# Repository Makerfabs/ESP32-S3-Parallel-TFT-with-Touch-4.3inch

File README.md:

# Makerfabs ESP32-S3 Parallel TFT with Touch 4.3inch

```c++
/*
Version:        V1.1
Author:            Vincent
Create Date:    2022/12/29
Note:
    2023/4/15 V1.2: Update V2.0 hardware.
    2023/1/10 V1.1: Update code to match the V1.3 hardware.
*/
```

[TOC]

# Makerfabs

[Makerfabs home page](https://www.makerfabs.com/)

[Makerfabs Wiki](https://wiki.makerfabs.com/)

# Makerfabs ESP32-S3 Parallel TFT with Touch 4.3inch

## Intruduce

Product Link ：[ESP32-S3 Parallel TFT with Touch 4.3"](https://www.makerfabs.com/esp32-s3-parallel-tft-with-touch-4-3-inch.html)

Wiki Link : [ESP32-S3 Parallel 4.3 TFT with Touch](http://wiki.makerfabs.com/ESP32_S3_Parallel_4.3_TFT_with_Touch.html)

This ESP32 4.3 inch IPS display could be an ideal displayer& controller for IoT applications. Its high lightness IPS display with a resolution of 800*480 makes the display effect beautiful, together with 5 points capacitive touch, great for applications such as home automation; There onboard SD card and RTC, to make it possible to record/play filed data. Also, there 2 Mabee/ Grove connectors, so the users can connect kinds of sensors to this board, to create personal prototype projects instantly.

The ESP32-S3 has WiFi& Bluetooth 5.0, and 8M PSRAM ESP32-S3 is used in this product, with 16M flash, to make it competent for more advanced applications.

## Feature

- Controller: ESP32-S3-WROOM-1, PCB Antenna, 16MB Flash, 8MB PSRAM, ESP32-S3-WROOM-1-N16R8
- On Board RTC
- Wireless: Wifi& Bluetooth 5.0
- LCD: 4.3 inch High Lightness IPS
- FPS: >30
- Resolution: 800*480
- LCD interface: RGB 565
- Touch Panel: 5 Points Touch, Capacitive
- Touch Panel Driver: GT911
- USB: Dual USB Type-C(one for USB-to-UART and one for native USB)
- USB to UART Chip: CP2104
- Power Supply: USB Type-C 5.0V(4.0V~5.25V)
- Button: Flash button and reset button
- Mabee interface: 1*I2C;1*GPIO
- MicroSD: Yes
- Arduino support: Yes
- Type-C Power Delivery: Not Supported
- Operation temperature: -40℃ to +85℃

## Version Attention

### V2.0

The codes has not been modified yet, please wait a little.

Still working...

|           | V2.0 | V1.3 |
| --------- | ---- | ---- |
| LCD_BLK   | NULL | 2    |
| I2S_DIN   | 19   | NULL |
| I2S_BCLK  | 20   | NULL |
| I2S_LRCLK | 2    | NULL |
|           |      |      |

Now the screen has no backlight PWM adjustment function, the pins are assigned to I2S. By default, the hardware backlight is always on.

### V1.3

V1.3 switches the touch screen RST and INT pins compared to V1.1 hardware.

```c++
// Hardware V1.3
#define TOUCH_GT911_SCL 18
#define TOUCH_GT911_SDA 17
#define TOUCH_GT911_INT -1
#define TOUCH_GT911_RST 38
```

### V1.1

If the silk screen on the back of your hardware is V1.1, follow the Branch V1.1 procedure.

# Code

## Complier Option

- Install board : ESP32 (Version 2.0.4)
- Install libraries：

- Use type-c use cable connect USB-TTL to PC.
- Select "ESP32-S3 DEV Module"
- Select PSRAM "OPI PSRAM"

"mf_Lvgl" library is modified from Lvgl library (version 8.3.2). 

Please unzip "lib/mf_Lvgl.zip" and copy to arduino library directory.

## Factory test program

examples\esp32s3_4.3_tft_fw_test

You can run this file test if you feel that your hardware is not working properly. You need to copy the images from the Images folder to the included TF card.

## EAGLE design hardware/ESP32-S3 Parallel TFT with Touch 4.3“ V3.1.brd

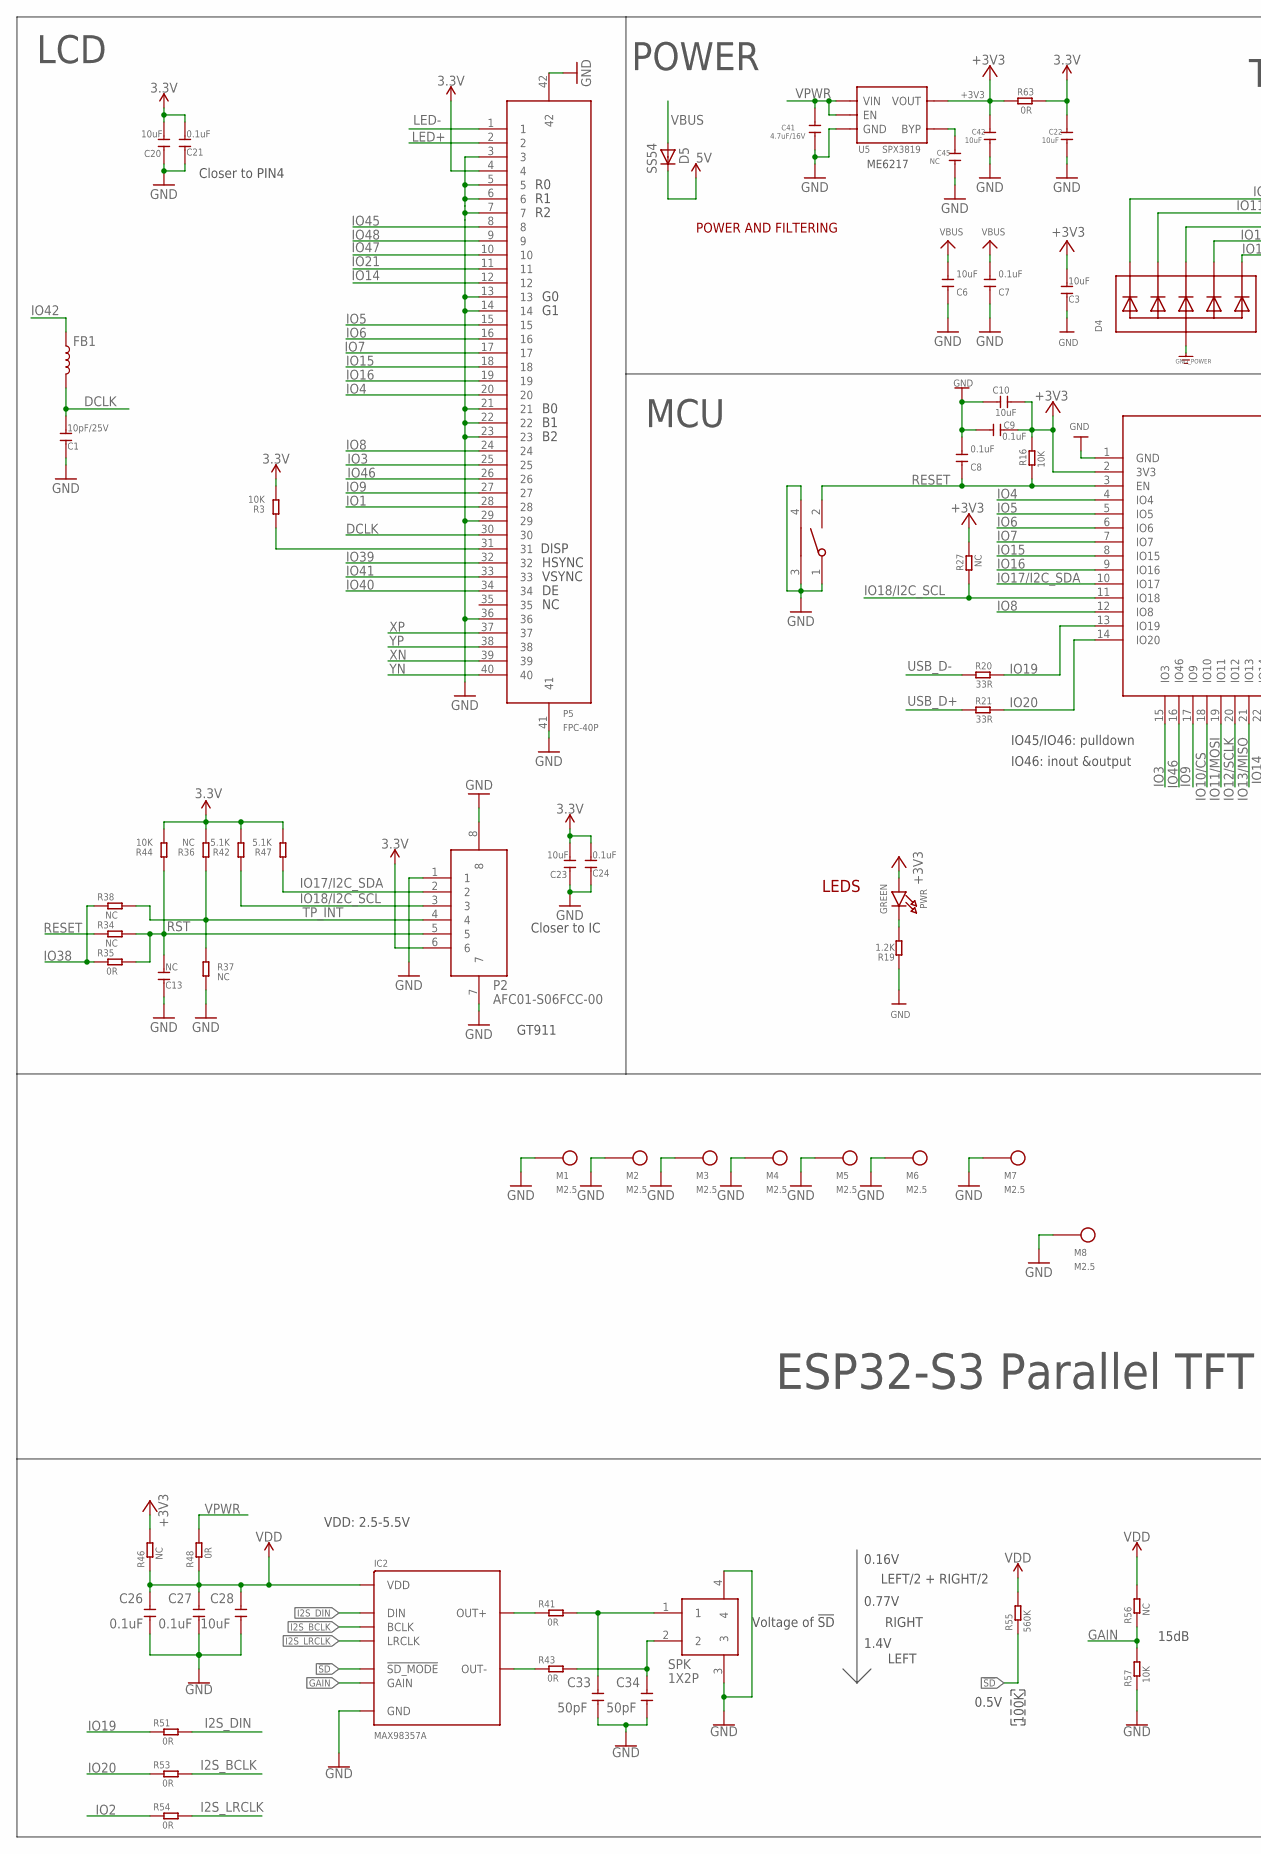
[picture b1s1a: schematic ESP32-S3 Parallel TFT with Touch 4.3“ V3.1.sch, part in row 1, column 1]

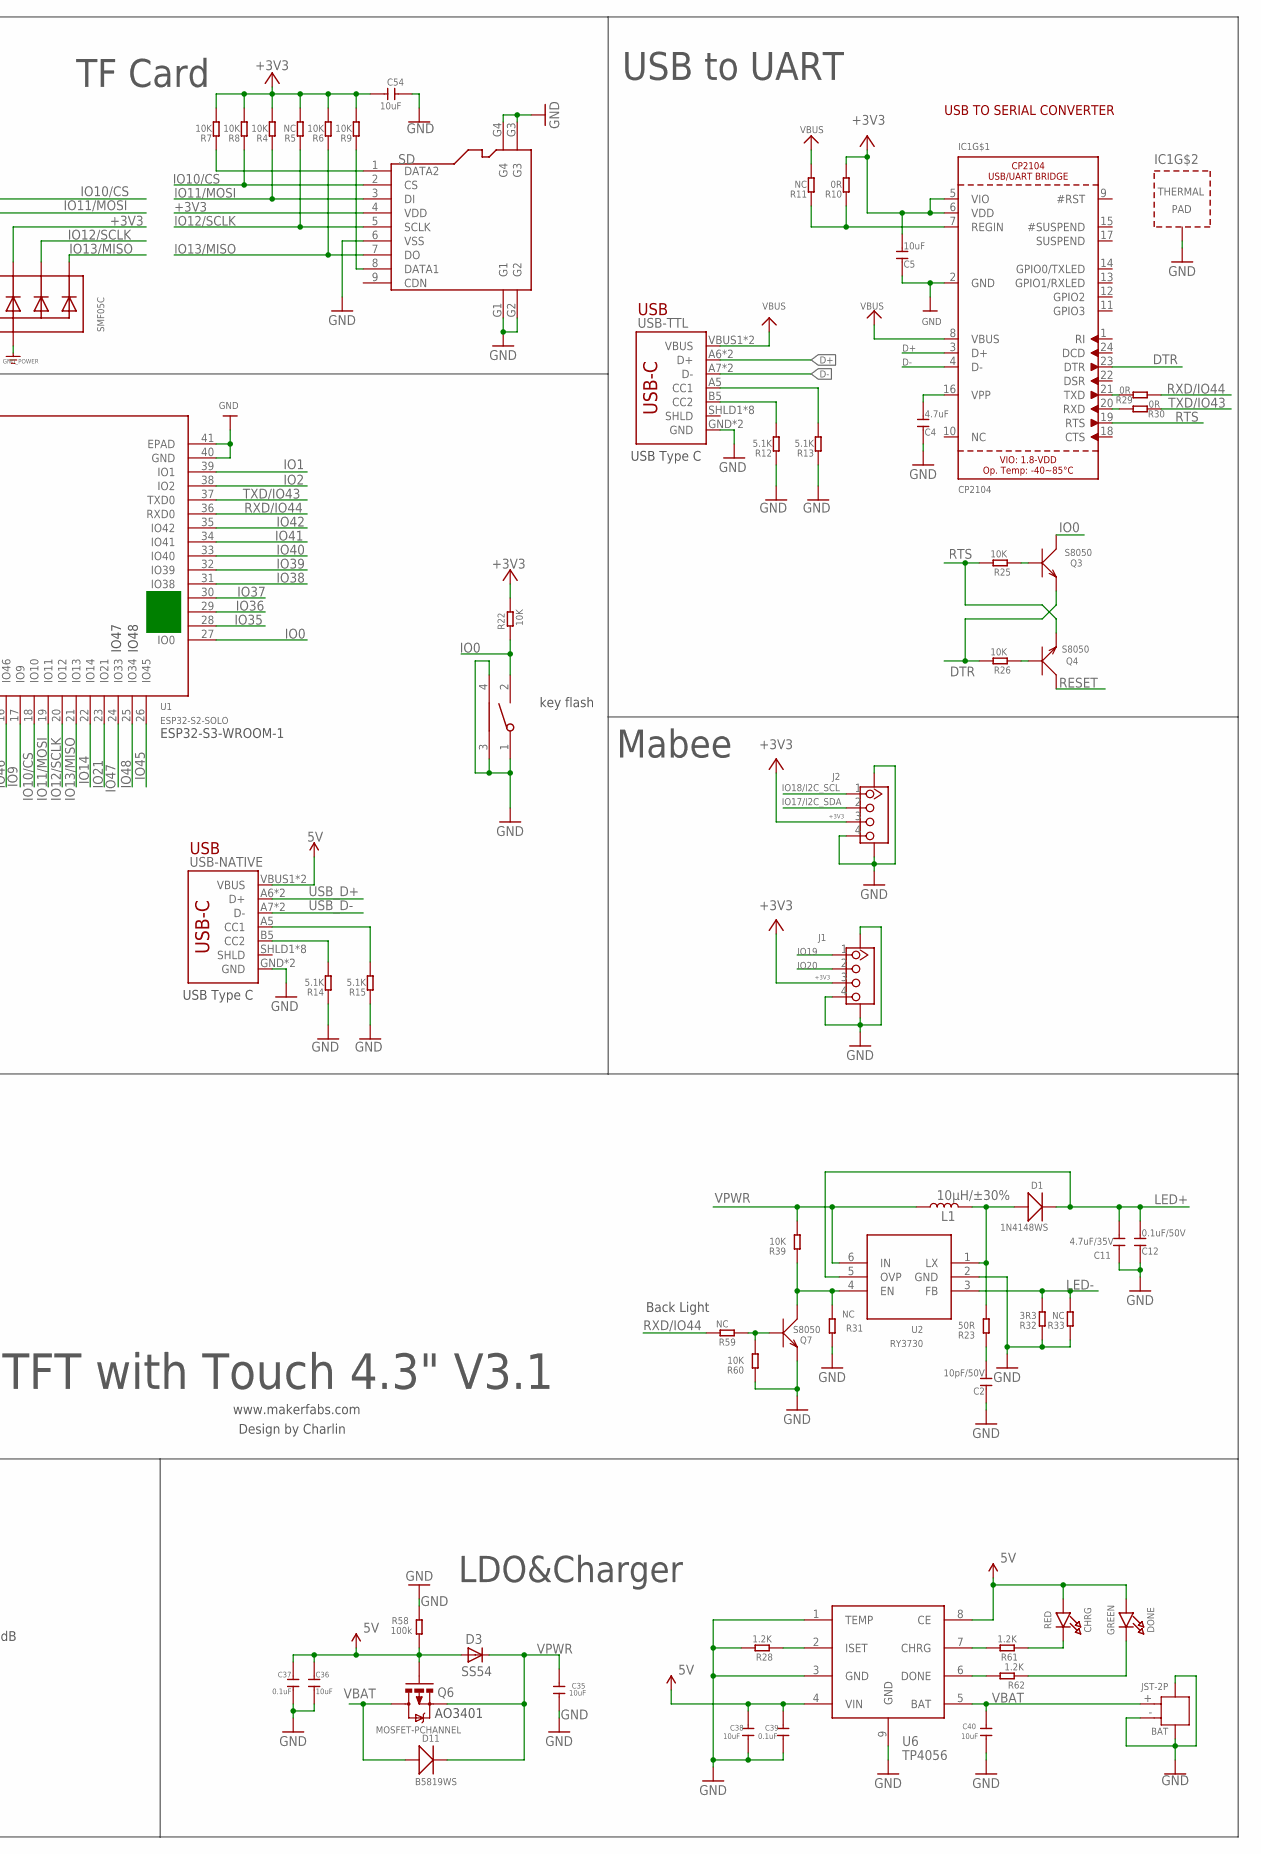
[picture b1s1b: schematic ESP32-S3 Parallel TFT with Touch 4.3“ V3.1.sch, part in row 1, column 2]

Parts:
BAT: JST-2P; HW2-SMD-2.0-90D
BOOT: TS24CA; 2*4*3.5MM
C1: 10pF/25V; DISCRETE_C0603
C2: 10pF/50V; DISCRETE_C0603
C3, C5, C6, C10, C20, C23, C54: 10uF; DISCRETE_C0603
C4: 4.7uF; DISCRETE_C0603
C7, C8, C9, C21, C24: 0.1uF; DISCRETE_C0603
C11: 4.7uF/35V; DISCRETE_C1206
C12: 0.1uF/50V; DISCRETE_C0603
C13: NC; DISCRETE_C0603
C22, C28, C35, C36, C38, C40, C42: 10uF; 0603
C26, C27, C37, C39: 0.1uF; 0603
C33, C34: 50pF; 0603
C41: 4.7uF/16V; 0603
C45: NC; 0603
CHRG: RED; CHIPLED_0805_NOOUTLINE
D1: 1N4148WS; SOD323
D3, D5: SS54; DO-214AC
D4: SMF05C; SOT363
D11: B5819WS; SOD323
DONE: GREEN; CHIPLED_0805_NOOUTLINE
FB1: INDUCTORFB-30OHM; 0603
IC1: CP2104; QFN24_4MM_SMSC
IC2: MAX98357A; TQFN-16
J1, J2: GROVE-CONNECTOR-SMD'90D'; HW4-SMD-2.0-90D
L1: 10µH/±30%; CR54
M1, M2, M3, M4, M5, M6, M7, M8: M2.5
P2: AFC01-S06FCC-00; SMD8-50P-740L535W
P5: FPC-40P; SMD42-50P-2560L490W
PWR: GREEN; CHIPLED_0805_NOOUTLINE
Q3, Q4, Q7: S8050; SOT23
Q6: MOSFET-PCHANNEL; SOT23-3
R3, R4, R6, R7, R8, R9, R39, R44, R60: 10K; DISCRETE_R0603
R5, R11, R31, R33, R36, R37, R59: NC; DISCRETE_R0603
R10: 0R; DISCRETE_R0603
R12, R13, R14, R15, R42, R47: 5.1K; DISCRETE_R0603
R16, R22, R25, R26, R57: 10K; R0603
R19: 1.2K; DISCRETE_R0603
R20, R21: 33R; R0603
R23: 50R; DISCRETE_R0603
R27, R34, R38, R46, R56: NC; R0603
R28, R61, R62: 1.2K; R0603
R29, R30, R35, R41, R43, R48, R51, R53, R54, R63: 0R; R0603
R32: 3R3; DISCRETE_R0603
R55: 560K; R0603
R58: 100k; R0603
RST: TS24CA; 2*4*3.5MM
SD: HOLDER-MICROSD-9P; 9P-SMD-W/-RING
SPK: 1X2P; 1X2P-SMT1.25MM
U1: ESP32­S2­SOLO; ESP32-­S2-­SOLO
U2: RY3730; SOT23-6
U5: SPX3819; SOT23-5
U6: TP4056; SOP8-1.27P
USB-NATIVE: USB_C5; USB-C-16P-5
USB-TTL: USB_C5; USB-C-16P-5

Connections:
3.3V: C20.2, C21.2, C22.1, C23.2, C24.2, P2.6, P5.4, R3.2, R36.2, R42.2, R44.2, R47.2, R63.2
5V: C36.2, C37.1, C38.1, C39.1, CHRG.A, D3.A, D5.C, DONE.A, Q6.1 (G), R58.1, U6.4 (VIN), U6.8 (CE), USB-NATIVE.VBUS1 (VBUS), USB-NATIVE.VBUS2 (VBUS)
!SD: IC2.P$4 (!SD_MODE), R55.1
+3V3: C3.2, C5.2, C9.1, C10.1, C42.1, C54.2, D4.4 (C3), IC1.5 (VIO), IC1.6 (VDD), J1.3, J2.3, PWR.A, R4.2, R5.2, R6.2, R7.2, R8.2, R9.2, R10.2, R16.2, R22.2, R27.2, R46.2, R63.1, SD.4 (VDD), U1.2 (3V3), U5.5 (VOUT)
D+: IC1.3 (D+), USB-TTL.A6 (D+), USB-TTL.B6 (D+)
D-: IC1.4 (D-), USB-TTL.A7 (D-), USB-TTL.B7 (D-)
DCLK: C1.2, FB1.2, P5.30
DTR: IC1.23 (DTR), Q3.2 (E), R26.2
GAIN: IC2.P$2 (GAIN), R56.1, R57.2
GND: BAT.3, BAT.4, BAT.- (2), BOOT.1, BOOT.3, BOOT.4, C1.1, C2.1, C3.1, C4.1, C5.1, C6.1, C7.1, C8.2, C9.2, C10.2, C11.1, C12.1, C13.1, C20.1, C21.1, C22.2, C23.1, C24.1, C26.1, C27.1, C28.1, C33.1, C34.1, C35.1, C36.1, C37.2, C38.2, C39.2, C40.2, C41.2, C42.2, C45.2, C54.1, D4.2 (A), IC1.2 (GND), IC1.THERM (TP), IC2.P$3 (GND), IC2.P$11 (GND), IC2.P$15 (GND), IC2.P$EP (GND), J1.4, J1.SS1, J1.SS2, J2.4, J2.SS1, J2.SS2, M1.1, M2.1, M3.1, M4.1, M5.1, M6.1, M7.1, M8.1, P2.1, P2.7, P2.8, P5.3, P5.5, P5.6, P5.7, P5.13, P5.14, P5.21, P5.22, P5.23, P5.29, P5.36, P5.41, P5.42, Q7.2 (E), R12.1, R13.1, R14.1, R15.1, R19.1, R28.2, R31.1, R32.1, R33.1, R37.2, R57.1, R58.2, R60.1, RST.1, RST.3, RST.4, SD.6 (VSS), SD.G1, SD.G2, SD.G3, SD.G4, SPK.3, SPK.4, U1.1 (GND), U1.40 (GND), U1.41 (EPAD), U2.2 (GND), U5.2 (GND), U6.1 (TEMP), U6.3 (GND), U6.9 (GND), USB-NATIVE.GND, USB-NATIVE.GND2 (GND), USB-TTL.GND, USB-TTL.GND2 (GND)
I2S_BCLK: IC2.P$16 (BCLK), R53.2
I2S_DIN: IC2.P$1 (DIN), R51.2
I2S_LRCLK: IC2.P$14 (LRCLK), R54.2
IO0: BOOT.2, Q3.3 (C), R22.1, U1.27 (IO0)
IO1: P5.28, U1.39 (IO1)
IO2: R54.1, U1.38 (IO2)
IO3: P5.25, U1.15 (IO3)
IO4: P5.20, U1.4 (IO4)
IO5: P5.15, U1.5 (IO5)
IO6: P5.16, U1.6 (IO6)
IO7: P5.17, U1.7 (IO7)
IO8: P5.24, U1.12 (IO8)
IO9: P5.27, U1.17 (IO9)
IO10/CS: D4.1 (C1), R8.1, SD.2 (CS), U1.18 (IO10)
IO11/MOSI: D4.3 (C2), R4.1, SD.3 (DI), U1.19 (IO11)
IO12/SCLK: D4.5 (C4), R5.1, SD.5 (SCLK), U1.20 (IO12)
IO13/MISO: D4.6 (C5), R6.1, SD.7 (DO), U1.21 (IO13)
IO14: P5.12, U1.22 (IO14)
IO15: P5.18, U1.8 (IO15)
IO16: P5.19, U1.9 (IO16)
IO17/I2C_SDA: J2.2, P2.2, R47.1, U1.10 (IO17)
IO18/I2C_SCL: J2.1, P2.3, R27.1, R42.1, U1.11 (IO18)
IO19: J1.1, R20.2, R51.1, U1.13 (IO19)
IO20: J1.2, R21.2, R53.1, U1.14 (IO20)
IO21: P5.11, U1.23 (IO21)
IO35: U1.28 (IO35)
IO36: U1.29 (IO36)
IO37: U1.30 (IO37)
IO38: R35.1, R38.1, U1.31 (IO38)
IO39: P5.32, U1.32 (IO39)
IO40: P5.34, U1.33 (IO40)
IO41: P5.33, U1.34 (IO41)
IO42: FB1.1, U1.35 (IO42)
IO45: P5.8, U1.26 (IO45)
IO46: P5.26, U1.16 (IO46)
IO47: P5.10, U1.24 (IO33)
IO48: P5.9, U1.25 (IO34)
LED+: C11.2, C12.2, D1.-, P5.2, U2.5 (OVP)
LED-: P5.1, R32.2, R33.2, U2.3 (FB)
unnamed: C4.2, IC1.16 (VPP)
unnamed: Q4.1 (B), R26.1
unnamed: Q3.1 (B), R25.1
unnamed: R15.2, USB-NATIVE.A5 (CC1)
unnamed: PWR.C, R19.2
unnamed: R13.2, USB-TTL.A5 (CC1)
unnamed: R12.2, USB-TTL.B5 (CC2)
unnamed: IC1.7 (REGIN), R10.1, R11.1
unnamed: R14.2, USB-NATIVE.B5 (CC2)
unnamed: D1.+, L1.P$2 (2), R23.2, U2.1 (LX)
unnamed: IC1.21 (TXD), R29.2
unnamed: IC1.20 (RXD), R30.2
unnamed: IC2.P$9 (OUT+), R41.1
unnamed: C2.2, R23.1
unnamed: IC2.P$10 (OUT-), R43.1
unnamed: Q7.3 (C), R31.2, R39.1, U2.4 (EN)
unnamed: C33.2, R41.2, SPK.1
unnamed: C34.2, R43.2, SPK.2
unnamed: P5.31, R3.1
unnamed: Q7.1 (B), R59.1, R60.2
unnamed: R28.1, U6.2 (ISET)
unnamed: R61.2, U6.7 (CHRG)
unnamed: R62.2, U6.6 (DONE)
unnamed: CHRG.C, R61.1
unnamed: DONE.C, R62.1
unnamed: R7.1, SD.1 (DATA2)
unnamed: R9.1, SD.8 (DATA1)
unnamed: C45.1, U5.4 (BYP)
RESET: C8.1, Q4.3 (C), R16.1, R34.1, RST.2, U1.3 (EN)
RST: C13.2, P2.5, R34.2, R35.2, R44.1
RTS: IC1.19 (RTS), Q4.2 (E), R25.2
RXD/IO44: R29.1, R59.2, U1.36 (RXD0)
TP_INT: P2.4, R36.1, R37.1, R38.2
TXD/IO43: R30.1, U1.37 (TXD0)
USB_D+: R21.1, USB-NATIVE.A6 (D+), USB-NATIVE.B6 (D+)
USB_D-: R20.1, USB-NATIVE.A7 (D-), USB-NATIVE.B7 (D-)
VBAT: BAT.+ (1), C40.1, D11.+, Q6.3 (D), U6.5 (BAT)
VBUS: C6.2, C7.2, D5.A, IC1.8 (VBUS), R11.2, USB-TTL.VBUS1 (VBUS), USB-TTL.VBUS2 (VBUS)
VDD: C26.2, C27.2, C28.2, IC2.P$7 (VDD), IC2.P$8 (VDD), R46.1, R48.1, R55.2, R56.2
VPWR: C35.2, C41.1, D3.C, D11.-, L1.P$1 (1), Q6.2 (S), R39.2, R48.2, U2.6 (IN), U5.1 (VIN), U5.3 (EN)
XN: P5.39
XP: P5.37
YN: P5.40
YP: P5.38

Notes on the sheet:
www.makerfabs.com
Design by Charlin
USB
LEDS
POWER AND FILTERING
USB TO SERIAL CONVERTER
key flash
ESP32-S3 Parallel TFT with Touch 4.3" V3.1
POWER
USB to UART
USB Type C
TF Card
GT911
Closer to IC
Back Light
IO45/IO46: pulldown
IO46: inout &output
Mabee
LCD
MCU
ESP32-S3-WROOM-1
IO47
IO48
Closer to PIN4
HSYNC
VSYNC
DISP
VDD: 2.5-5.5V
0.16V
0.77V
1.4V
LEFT/2 + RIGHT/2
RIGHT
LEFT
0.5V
100K
15dB
Voltage of !SD
LDO&Charger
AO3401

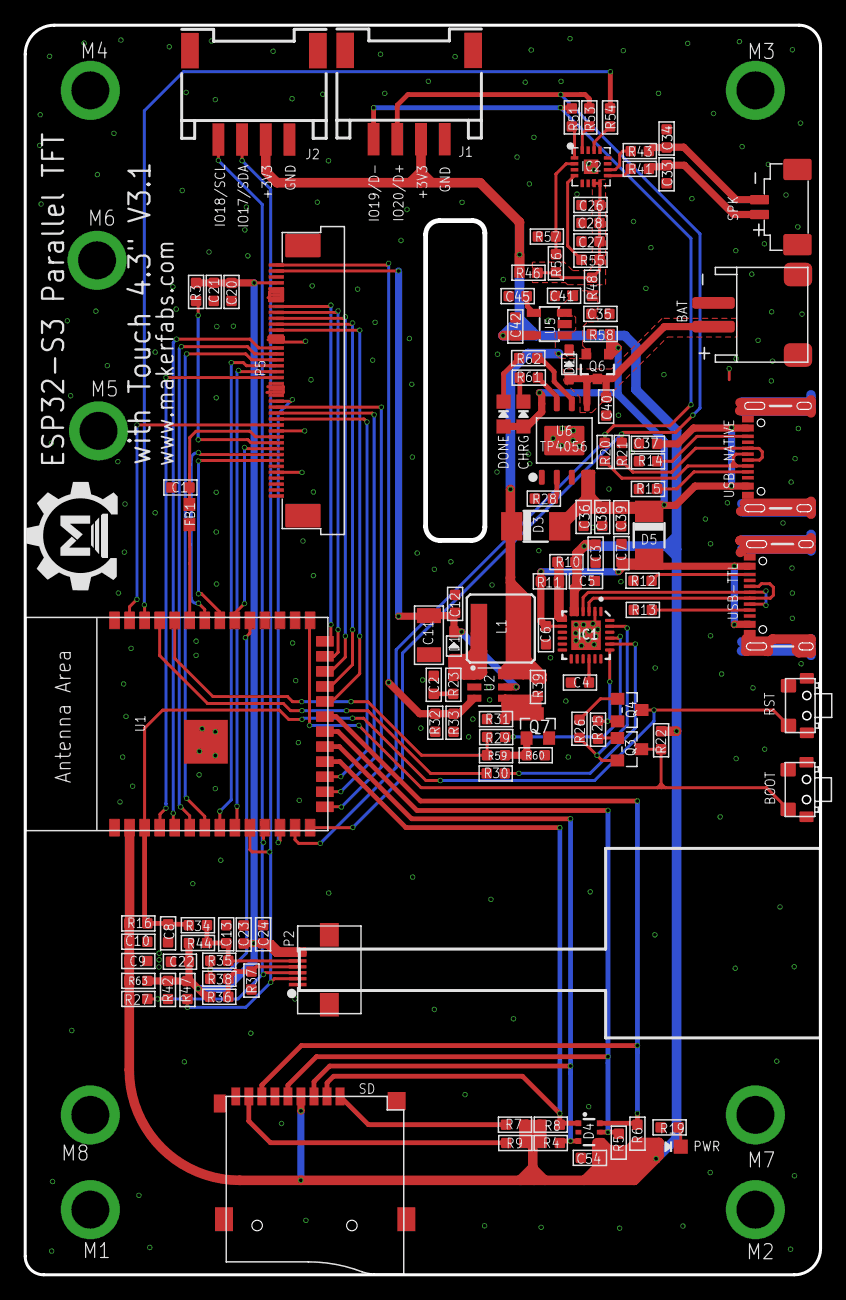
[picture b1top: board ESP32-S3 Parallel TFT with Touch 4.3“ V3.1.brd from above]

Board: 2 copper layers, 67.2 x 105.5 mm, 126 parts (0 on the bottom side), 86 nets.

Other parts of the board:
U$1: MAKERFABS_0.3

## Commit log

2022-12-10 Default firmware
2022-12-10 add hardware and images for display
2022-12-10 add examples
2022-12-10 add datasheet of Display
2022-12-20 hid keyboard example
2022-12-21 Add gif display
2022-12-30 Edit readme
2023-01-03 Add I2C wire scan and backlight controll
2023-01-10 V1.3 Pin Change
2023-01-10 V1.3 Pin change and code fix
2023-01-10 Edit readme v1.1
2023-01-11 V1.3 hardware update
2023-03-02 Add LovyanGFX demo
2023-04-07 Add demo
2023-04-15 V2.0 Hardware
2023-04-17 Change code for hardware 2.0
2023-04-17 Hardware 2.0 confirm
2023-06-08 v3.1
2023-07-11 Update hardware
2023-10-24 Fix bug
2024-03-13 Add some note
2025-12-23 add esp-idf example
2025-12-29 add example for use squreline and idf
2026-01-13 fix README.md

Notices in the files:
parts and their libraries:
microbuilder: This work is placed in the public domain, and may be freely used for commercial and non-commercial work with the following conditions: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
SparkFun-Coils: Licensing: Creative Commons ShareAlike 4.0 International - https://creativecommons.org/licenses/by-sa/4.0
